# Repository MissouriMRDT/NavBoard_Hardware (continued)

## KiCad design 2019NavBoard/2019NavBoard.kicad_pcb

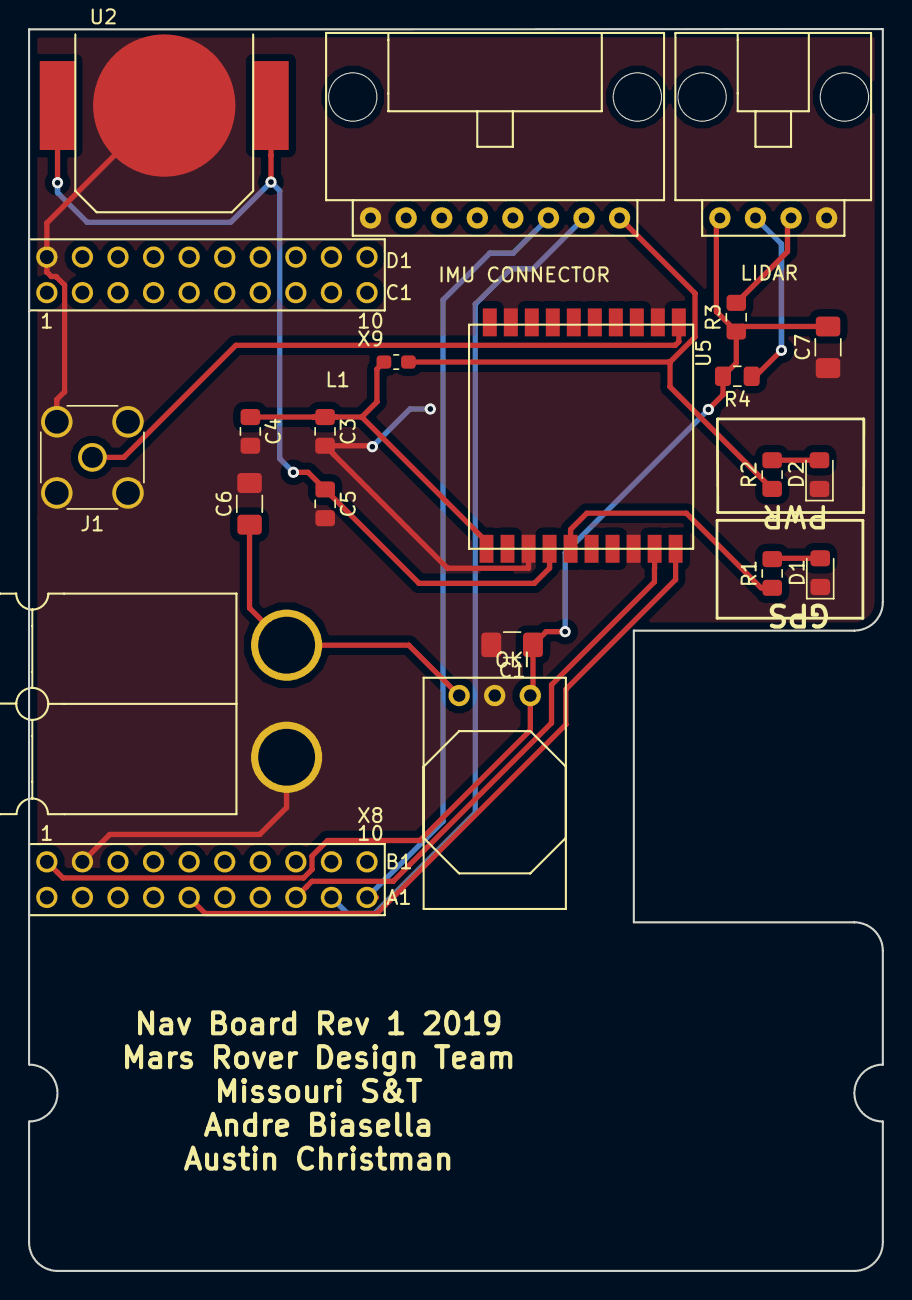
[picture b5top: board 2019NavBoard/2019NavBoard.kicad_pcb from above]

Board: 2 copper layers, 61.0 x 88.7 mm, 21 parts (0 on the bottom side), 16 nets.

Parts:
C1, C6: 10uF; C_1206_3216Metric_Pad1.42x1.75mm_HandSolder
C2: OKI; OKI_Horizontal
C3, C5: 1uF; C_0805_2012Metric_Pad1.15x1.40mm_HandSolder
C4: 0.01uF; C_0805_2012Metric_Pad1.15x1.40mm_HandSolder
C7: 680uF; C_1206_3216Metric_Pad1.42x1.75mm_HandSolder
Conn1: AndersonPP; Anderson_2_Horisontal_Side_by_Side
D1: FIX; LED_0805_2012Metric_Pad1.15x1.40mm_HandSolder
D2: PWR; LED_0805_2012Metric_Pad1.15x1.40mm_HandSolder
IMU CONNECTOR: Molex_SL_08; MOLEX_SL_08_Horizontal
J1: Conn_Coaxial; SMA_Amphenol_132134-16_Vertical
L1: INDUCTOR; L_0603_1608Metric_Pad1.05x0.95mm_HandSolder
LIDAR: LiDAR; MOLEX_SL_04_Horizontal
R1, R2: 1K; R_0805_2012Metric_Pad1.15x1.40mm_HandSolder
R3, R4: 4.7K; R_0805_2012Metric_Pad1.15x1.40mm_HandSolder
U1: TM4C129E_Launchpad_X9
U2: 12mm_Coin_Battery_Cell_Holder; CR1220_Battery_Holder
U5: FGPMMOPA6H

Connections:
+3V3: IMU CONNECTOR.8, L1.1, R2.1, U1.+3V3
+5V: C1.1, C2.3, C7.2, LIDAR.1, R3.1, R4.2, U1.+5V
GND: C1.2, C2.2, C3.2, C4.2, C5.2, C6.2, C7.1, Conn1.1, D1.1, D2.1, IMU CONNECTOR.1, J1.2, LIDAR.4, U1.GND, U2.2, U5.3, U5.8, U5.12, U5.19
LIDAR_SCL: LIDAR.2, R4.1
LIDAR_SDA: LIDAR.3, R3.2
unnamed: C2.1, C6.1, Conn1.2
unnamed: C3.1, C4.1, L1.2, U5.1
unnamed: D1.2, R1.2
unnamed: D2.2, R2.2
unnamed: J1.1, U5.11
unnamed: R1.1, U5.5
RX(7): U1.PC6, U5.10
SCL(0): IMU CONNECTOR.7, U1.PB2
SDA(0): IMU CONNECTOR.6, U1.PB3
TX(7): U1.PC7, U5.9
VBACKUP: C5.1, U2.1, U5.4

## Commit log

2015-10-05 Added GPS Schematic
    Added my version of the GPS thingy
2015-10-05 Added GPS Schematic
    My version
2015-10-19 Placed the distance between the headers
2015-10-24 Finished first rev of the gps board
    Shout out to board space and Judah
2015-10-26 Revision 1 of the GPS Board
    Super EAGLE Training
2015-10-26 Created my first board!
2015-10-26 Added bill of materials
    Here is the components to be put on the board
2015-10-26 Updated the folder structure
    Gave everyone there one folder
2015-10-26 Added a git ignore
2015-10-26 Updated the git ignore and tested the files
2015-10-31 Added all board files and things
2016-01-22 Updated BOM
2016-01-22 Added 3-Pin Connector
    Give this a look Judah and let me know if you need more stuffs
2016-03-14 swapped power conn to app45 and put backup battery on top, gen'ed gerbers
2016-10-13 Removed unnessasary files and file structure
2016-10-13 Renamed Board and Schematic files
2016-10-13 Deleted Bill of Materials
2016-10-13 Updated the .gitignore
2016-11-05 Added new NavBoard file, Removed old Navigation Board files
2016-11-05 Added LSM9DS1 IMU to circuit
    Wired up the IMU breakout board to Tiva and changed RX and TX notation
    tags to RX(2) and TX(2).
2016-11-05 Completed first version of PCB design and added power connectors and regulator to schematic and board
    Completed first version of board design, added 12v anderson connectors
    to schematic along with 5v regulator and 10 uF capacitors, and changed
    RX(2) and TX(2) to RX(6) and TX(6).
2016-11-07 Finished revision 1 of board design
    Schematic: Connected INTM, INT1, INT2, and DRDYM from IMU to pins PL0
    through PL3 on the Tiva. Added two new capacitors to power input of the
    GPS chip. Added a capacitor to the battery power supply.
    Board: Added top layer ground plane with ground plane stitching, added
    mounting holes for the navigation board, arranged all component names on
    board so they would be visible once they were silk screened, and added
2018-05-03 Added BOM.csv
2018-10-13 GPS chip/LSM9DS1 created
2018-10-13 Fixed libraries
2018-10-13 Remade, finished schematic
2018-10-13 Started editing netlist
2018-10-14 saved wor
2018-10-14 Assigned all parts
2018-10-14 Finalized high lvl schematic
2018-10-16 Fixed cut lines on PCB layout
2018-10-20 Fixed Errors and added a LIDAR
    Some of the gobal labels had to be fixed and I added a LIDAR to the schematic. Also added some .txt files for pdr.
2018-10-20 Made updates to txt files
2018-10-23 Added LIDAR 4SL
2018-10-23 Changed Txt files
2018-10-23 Final PDR edits
2018-10-25 Changed indicators
2018-10-26 PDR Ready
2018-11-03 Added Tracks
2018-11-04 Slight changes to PCB traces
2018-11-11 Finalized Rev1
2018-11-13 Edit traces
2018-11-15 Edit traces before review
2018-11-15 modified gitignore
2018-11-16 After meeting
2018-11-16 Deleted Eagle Files
2018-11-18 Deleted old files, renamed files to NavBoard Hardware
2018-11-18 Renamed more files to NavBoard_Hardware
2018-11-18 Moved txt files and renamed files
2018-11-18 Rename
2018-12-01 fixed file errors
2018-12-01 revised schematic after meeting
2018-12-02 NOTES
2018-12-09 redid files again
2018-12-09 Did good work
2018-12-10 Editied schematic and made PCB
2018-12-10 edit PCB
2018-12-15 Fixed traces
2018-12-15 rev1
2018-12-16 worked on Board
2018-12-16 BOM and other files for review
2018-12-16 just in case push
2018-12-18 fxed gitignore
2019-02-11 added todo
2019-02-15 Updated to rev2 libraries
2019-02-15 updated rev 2 libraries
2019-02-15 generated step file
2019-02-18 Update ToDo rev 2.txt
    Added LiDAR-specific high-level changes needed
2019-02-21 Update ToDo rev 2.txt
    Updates rev2 in regards to LiDAR.
2019-02-25 3v3 lidar
2019-02-26 ATMEGA328P update
2019-02-26 added comments
2019-03-02 Finsihed all changes by Andrew Starting PCB
2019-03-02 Traces and PCB begin
2019-03-02 Retracing PCB for Rev 2
2019-03-03 REV2
2019-03-03 made board super dank
2019-03-03 Board Review
2019-03-03 Push
2019-03-03 CURRENT REVISION
2019-03-03 3.3 to 5 volt converter added
2019-03-03 added footprints
2019-03-03 saved
2019-03-03 molex 2 added
2019-03-03 Added level shifter to board and made traces beautiful
    I, Andre did alot. I sleep now
2019-03-04 Fine tooth comb
2019-03-04 fixed direction of signs
2019-03-04 nitpicking
2019-03-04 PCB UPDATES
2019-03-04 REV 2
2019-03-04 final push
2019-03-04 gerbs
2019-03-04 Final touches
2019-03-04 Added 3.3V output to IMU on layout
2019-03-04 Made many small tweaks
2019-03-05 minor changes and improvements
2019-03-05 BOM MADE
2019-03-05 saved sch
2019-03-05 Fixed DRC Polygons
2019-03-05 Stitched GND plane & gen Gerbs
2019-03-19 Rev 3 start
2019-03-20 Made both sides ground and fixed wires
2019-03-24 Rev 3 Gerbs and Minor Changes made
2020-09-12 created project
2021-01-08 Placed components and started BNO055 schematic
2021-01-09 Completed the schematic for the IMUs but still need to add indicators and have a schematic review.
2021-01-09 Finished Layout but needs review
2021-01-09 Started Layout
2021-01-10 Layout almost finished just need to complete LED traces.
2021-01-10 Finished Layout but I still need to complete the BOM and generate GERBs.
2021-01-10 Completed the board but still needs a review.
2021-01-13 Added readme and fixed serial flags in the schematic
2021-10-09 Duplicated last year's board with a few changes
    BMX160 was replaced with BNO080 and LiDAR circuit was removed. Reorganized schematic and cleaned up some wires.
2021-10-15 Finished wiring BNO080 circuit
    Also changed values of indicator resistors
2021-10-16 Changed BNO080 to I2C communication
2021-10-23 PDF Schematic
    Uploaded PDF Schematic to Github
2021-10-24 Added backup battery for GPS
    Change was discussed in PDR. Also fixed input to BNO080.
2021-11-04 Assigned footprints and started layout
2021-11-15 Finished layout for board reviews
2021-11-16 Board Review Edits
2021-11-16 Deleted old components
2021-11-17 Downloaded footprints and libraries, wired GPS
2021-11-17 Completed schematic
2021-11-18 Completed Layout
2021-11-19 CDR Changes 2
    Ready to release, signatures to be added
2021-11-21 Signature
    Added my signature on the board. Still needs one more.
2021-11-21 Fixed Signature
2021-11-21 Added signature
    Final updates, ready to order
2021-12-30 removed rescue libraries & fixed symbol associations. imported IMU footprints to MRDT_KICAD_LIBRARIES
2022-09-07 Initial pass at stackable arrangement
    Attempting to replace previous board design with 2 daughter boards, using a Teensy 4.1 instead of a Raspberry Pi
2022-09-14 Symbol Stuff
2022-09-14 Fixed broken symbols
2022-09-15 Moved status LEDs to Raspberry Pi GPIO
2022-09-15 Replaced global labels with net labels
2022-09-15 Added title block info, adjusted powerpole connectors
2022-09-15 Added links to IC datasheets
2022-09-15 Added pulldown resistors to unused pins of BHI160B
2022-09-15 Added test points and pulldown resistors to unused pins of ICM-20608
2022-09-15 Routed ICs and their passive components
2022-09-15 Corrected 3D models, added model of Raspberry Pi
2022-09-15 Routed most components
    Some power traces, and LEDs remain
2022-09-16 Component placement done (except LEDs), redesign of schematic pages, started documentation presentations
    Leaving @katdun14 and @nvngx responsible for routing the status LEDs.
2022-09-17 Added ground vias for added isolation in substrate, worked on schematic review 1 powerpoint
2022-09-17 Added Information To Voltage Regulator Component Sheets, Improved Schematic Review 1 Powerpoint
2022-09-17 Improved Schematic
2022-09-17 Swapped TX and RX for GPS pins
2022-09-18 Redesigned layoput
2022-09-22 Routed LEDs
2022-09-22 Added name and moved words
2022-09-23 Adjusted LED silkscreen
2022-09-23 Adjusted silkscreen for various components
2022-09-23 Adjusted copper pour
2022-09-23 Updated sheet title info
2022-09-23 Updated Schematic Review 1 Powerpoint
2022-09-23 Corrected accelerometer regulator capacitors
2022-09-23 Included BOM to Schematic Review 1 PowerPoint
2022-09-23 Added signatures to pcb silkscreen
2022-09-24 Added 0ohm resistors to I2C
2022-09-26 Added signage for TSR power supplies
2022-10-01 Made PDF
2022-10-07 Created adapter symbols and footprints
2022-10-07 Added connectors, cleaned up file directory
2022-10-07 Updated BMI component sheet from Navboard_2023_rev2
2022-10-07 Most schematic connections completed
2022-10-07 Annotated Schematic, assigned footprints, recovered accelerometer footprints
2022-10-07 Fixed pinout of 24pin-to-16pin adapter footprint
2022-10-07 Corrected pinout of RJ45 symbol, squashed some bugs
2022-10-07 Progress with PCB layout
2022-10-07 Resized Ethernet to 2.54mm
2022-10-08 Placed and aligned all headers
2022-10-08 Placed OKI SMD components, aligned ethernet pins
2022-10-09 Completed routing, added 3D models to IMUs
2022-10-09 Adjusted silkscreen labels
2022-10-09 Added 3D models for pin sockets and headers
2022-10-09 Rearranged PCBs, added mouse bites
2022-10-09 Annotated schematic pages
2022-10-09 Added signage to pcb silkscreen
2022-10-09 Generated 3D renderings, animation, and schematic review PowerPoint
2022-10-09 Plotted schematic to pdf
2022-11-01 Initial changes and prototyping the new layout
2022-11-01 Rearranged schematic
    I realize now that this is a dumb idea...
    Going to redesign the board so the teensy just sits on top
2022-11-03 Decided on pcb layout
2022-11-03 Realized this could all fit on a single board
2022-11-03 Most connections made on schematic
2022-11-03 Completed routing, finalized schematic
2022-11-03 Updated schematic page text
2022-11-04 Made I2C pulldown resistors pullup instead
2022-11-05 Square powerpole footprints
2022-11-05 Cleaned up unnecessary files
2022-11-19 generated gerbs
2022-11-19 forgot to zip gerbs
2022-11-25 Added pcb dimensions, images of board, readme files
2022-11-25 Added images to readme files
2022-11-25 Updated repo with up-to-date schematic and pcb
    Not sure why this happened, but the repo should be up to date now. We should try to cancel the PCB order and reupload this board if that's still possible.
2022-11-25 Generated images, edited Readme files
